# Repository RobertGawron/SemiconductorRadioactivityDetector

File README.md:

# Semiconductor Radioactivity Detector

## Summary

There are many ways to measure radioactivity levels. Semiconductor detectors sense interactions between ionizing radiation and a p-n junction. Since most hobbyists use Geiger-Muller-based detectors (which are lamp-based devices, not semiconductors), I think it's a cool idea to explore this semiconductor-based approach.

## System Architecture

## Additional sub-components used

### Hardware Data Logger

A pulse counter based on the STM32 and ESP chips that can send the measurements via WiFi for further processing, store them on an SD card, or display them to the user. This is an [open-source and open-hardware project that I created, available on GitHub.](https://github.com/RobertGawron/HardwareDataLogger)

### Auxiliary Board (Power Supply + Logic Level Converter)

An auxiliary board was developed later on to fix things that weren’t included on the original board (because it's easier to add a new board than to rework the whole device). This board isn’t really a successful one, but it does its job. It has:

**12V power supply (powered from a 15V wall adapter).** The device needs a very low-noise power supply. Originally, it was powered by a high-quality lab power supply. However, to make it more versatile, I tried using a cheap Chinese power supply and add a board with a power regulator. 

In the first revision, I chose the NCP1117 stabiliser, but it was too noisy. This caused the sensor's output to oscillate randomly, which made the device rather pointless. I made it work by adding plenty of capacitors on the input and output, though this was always a temporary solution. 

In the new version, I will be replacing it with the TPS7A2601DRVR.

**Logic level converter,** to convert logic levels from 12V (high) and 0V (low)—as output by the sensor—to 3.3V (high) and 0V (low), which is standard for STM32 and cheap Chinese logic analyzers. 

In the first version, I just used an open-collector configuration, but this made the device unable to work directly with cheap 3.3V logic analyzers, which need either 0V (low state) or 3.3V (high state).

In the new version, I added a cheap 3.3V stabiliser to provide the correct high state.

## Hardware

All hardware was done using KiCad.

The sensor assembly needs care, as this device is extremely sensitive; [more details are presented in this README.](./Hardware/SemiconductorRadioactivityDetector/README.md)

The sensor circuit is shown below.

The new design of the auxiliary board is shown below, integrated with the whole device. It's the small PCB on the right side of the image. The render was done using Blender.

Circuit of the Auxiliary Board is shown below.

## Mechanic

Before ordering PCBs and the 3D print for the auxiliary holder, how could I be sure everything would fit? Instead of redoing things many times, I took the model of the old PCB, the new PCB that would be the addition to it, the 3D holder, and the metal enclosure (which is a popular consumer enclosure), placed them all accordingly in Blender, and checked if everything fit.

[The needed tools and the workflow are presented in this README.](./Mechanic/README.md)

## Software

[There are some Python and R scripts available](./Software/DataAcquisition/) for gathering data from the device. These were developed during the initial testing phase and may still be useful due to their simplicity.

In the future, the goal is to transition to using the [Hardware Data Logger](https://github.com/RobertGawron/HardwareDataLogger), which provides a more versatile and efficient way to collect measurements.

## Project History

 * [First Unsuccessful Attempts](https://robertgawron.blogspot.com/2016/12/semiconductor-radioactivity-detector.html)
semiconductor-radioactivity-detector.html) - the biggest issue was the lack of proper shielding. Due to the extremely high amplification levels, the device either failed to function or began oscillating uncontrollably without adequate shielding.
* [First Working Version](https://robertgawron.blogspot.com/2019/02/semiconductor-radioactivity-detector.html) - this was a simplified version of the current project. It lacked both polarization voltage and an ADC converter, but it laid the foundation for further improvements.

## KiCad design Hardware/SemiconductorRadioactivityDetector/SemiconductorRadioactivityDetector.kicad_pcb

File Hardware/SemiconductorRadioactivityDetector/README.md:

# Extra Modifications

* The device needs to be completely shielded from sunlight and electromagnetic interference. It should be placed in a grounded metal case. Where the sensor is located, a hole should be drilled and covered with aluminum foil. This taped hole is necessary because the metal enclosure is too thick and would block too much of the radiation. The foil is needed because the signal from sunlight is much stronger, and it would overwhelm the sensor, effectively turning it into a light detector.
* As close as possible to the input power socket, I placed 1n/16V and 100n/16V capacitors in parallel. Without them, the device began oscillating randomly.
* A Schottky diode is connected in series after the extra capacitors mentioned above to reduce the risk of damaging the device when the power supply is connected incorrectly. I'm not sure if it will help enough, but I’ve already damaged one PCB this way, so now it's included.

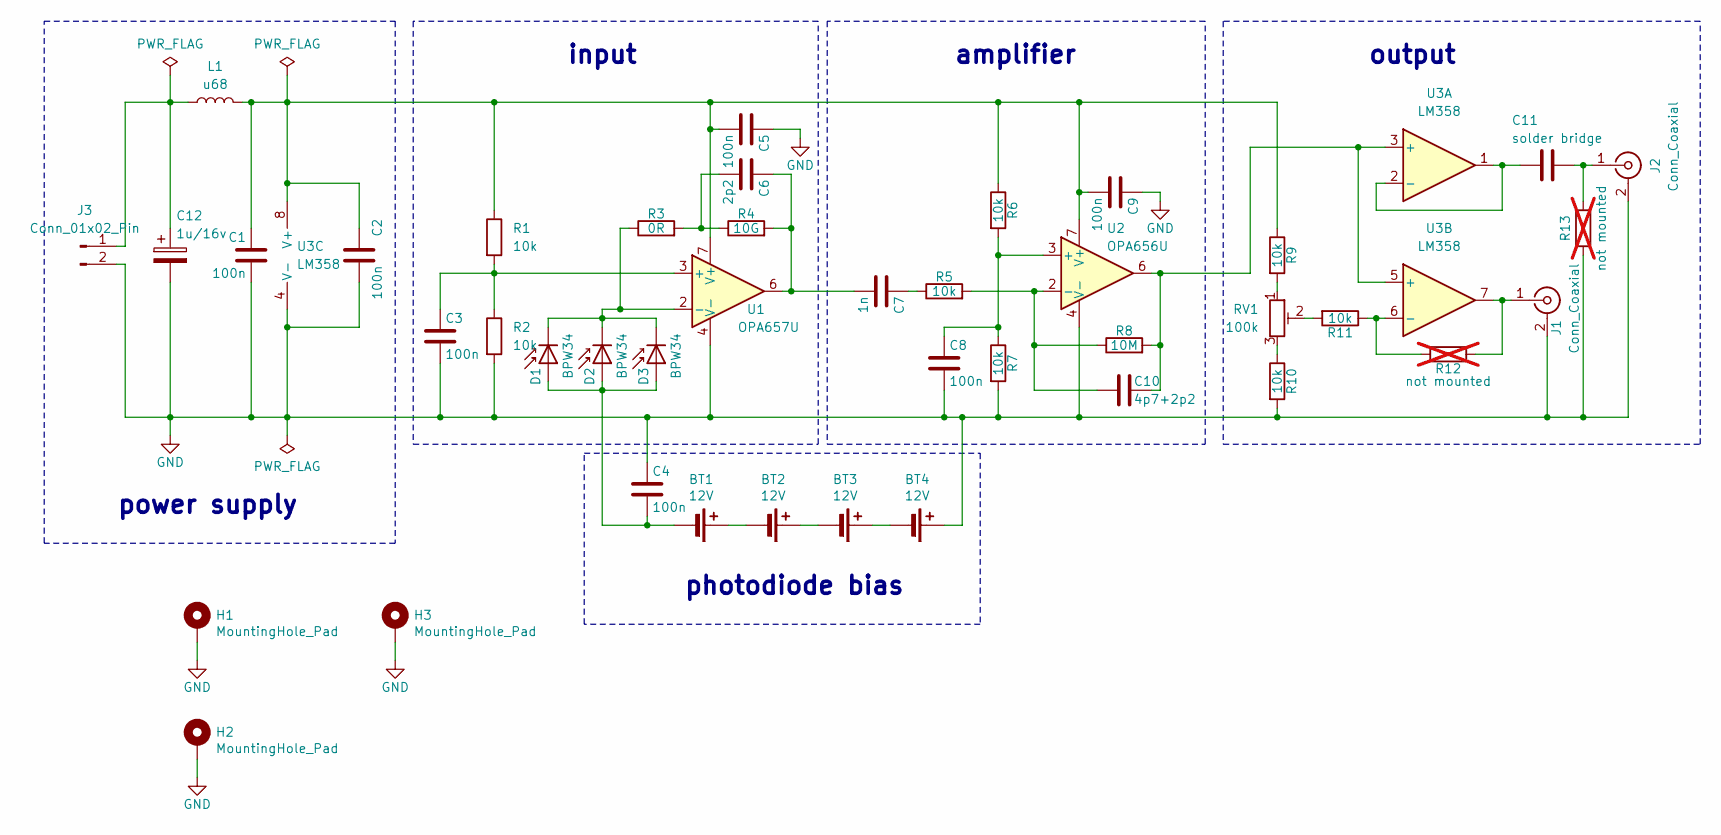
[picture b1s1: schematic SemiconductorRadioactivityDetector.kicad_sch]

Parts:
BT1, BT2, BT3, BT4: 12V; A23Single
C1, C3, C4, C5, C8: 100n; C_0805_2012Metric
C2, C9: 100n; C_0805_HandSoldering
C6: 2p2; C_0805_2012Metric
C7: 1n; C_0805_2012Metric
C10: 4p7+2p2; C_0805_HandSoldering
C11: solder bridge; C_0805_2012Metric
C12: 1u/16v; CP_EIA-3216-18_Kemet-A
D1, D2, D3: BPW34; D_DO-35_SOD27_P5.08mm_Vertical_KathodeUp
H1, H2, H3: MountingHole_Pad; MountingHole_3.5mm_Pad
J1, J2: Conn_Coaxial; BNC_PanelMountable_Vertical
J3: Conn_01x02_Pin; PinHeader_1x02_P2.54mm_Vertical
L1: u68; L_1812_4532Metric
R1, R2, R5, R7, R9, R10, R11: 10k; R_0805_HandSoldering
R3: 0R; R_0805_HandSoldering
R4: 10G; R_0805_HandSoldering
R6: 10k; R_Axial_DIN0207_L6.3mm_D2.5mm_P10.16mm_Horizontal
R8: 10M; R_0805_HandSoldering
R12, R13: not mounted; R_0805_HandSoldering; not fitted
RV1: 100k; Potentiometer_Bourns_3296W_Vertical
U1: OPA657U; SOIC-8_3.9x4.9mm_Pitch1.27mm
U2: OPA656U; SOIC-8_3.9x4.9mm_Pitch1.27mm
U3: LM358; SOIC-8_3.9x4.9mm_P1.27mm

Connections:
GND: BT4.1 (+), C1.2, C2.2, C3.2, C4.1, C5.1, C8.2, C9.1, C12.2, H1.1, H2.1, H3.1, J1.2 (Ext), J2.2 (Ext), J3.2, R2.2, R7.2, R10.2, R13.2, U1.4 (V-), U2.4 (V-), U3.4 (V-)
unnamed: BT1.1 (+), BT2.2 (-)
unnamed: BT1.2 (-), C4.2, D1.2 (A), D2.2 (A), D3.2 (A)
unnamed: BT2.1 (+), BT3.2 (-)
unnamed: BT3.1 (+), BT4.2 (-)
unnamed: C6.1, C7.2, R4.2, U1.6
unnamed: C6.2, R3.2, R4.1
unnamed: C7.1, R5.1
unnamed: D1.1 (K), D2.1 (K), D3.1 (K), R3.1, U1.2 (-)
unnamed: J1.1 (In), R12.1, U3.7
unnamed: C11.1, J2.1 (In), R13.1
unnamed: C12.1, J3.1, L1.1
unnamed: R9.2, RV1.1
unnamed: R10.1, RV1.3
unnamed: R11.2, RV1.2
unnamed: C3.1, R1.2, R2.1, U1.3 (+)
unnamed: C1.1, C2.1, C5.2, C9.2, L1.2, R1.1, R6.1, R9.1, U1.7 (V+), U2.7 (V+), U3.8 (V+)
unnamed: C8.1, R6.2, R7.1, U2.3 (+)
unnamed: C10.2, R5.2, R8.1, U2.2 (-)
unnamed: C10.1, R8.2, U2.6, U3.3 (+), U3.5 (+)
unnamed: C11.2, U3.1, U3.2 (-)
unnamed: R11.1, R12.2, U3.6 (-)

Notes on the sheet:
input
amplifier
power supply
output
photodiode bias

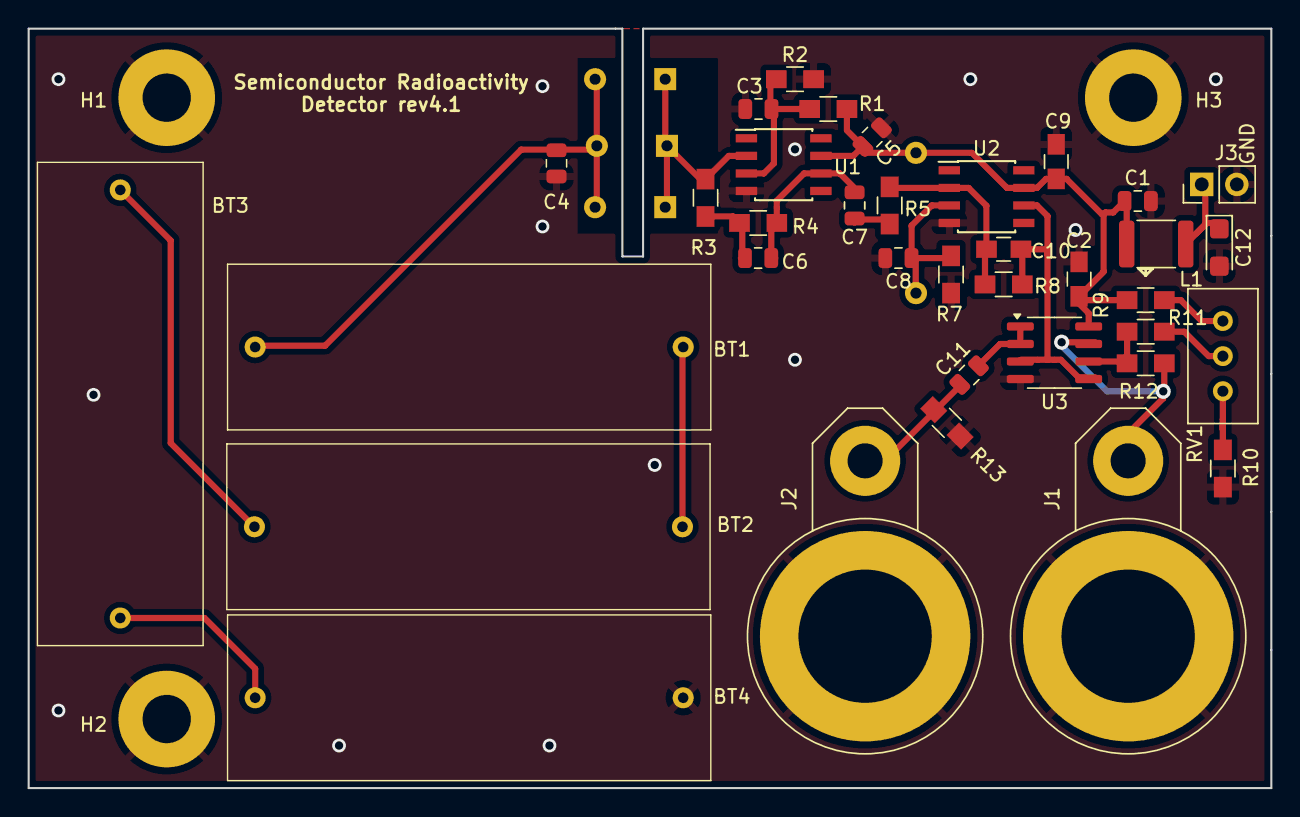
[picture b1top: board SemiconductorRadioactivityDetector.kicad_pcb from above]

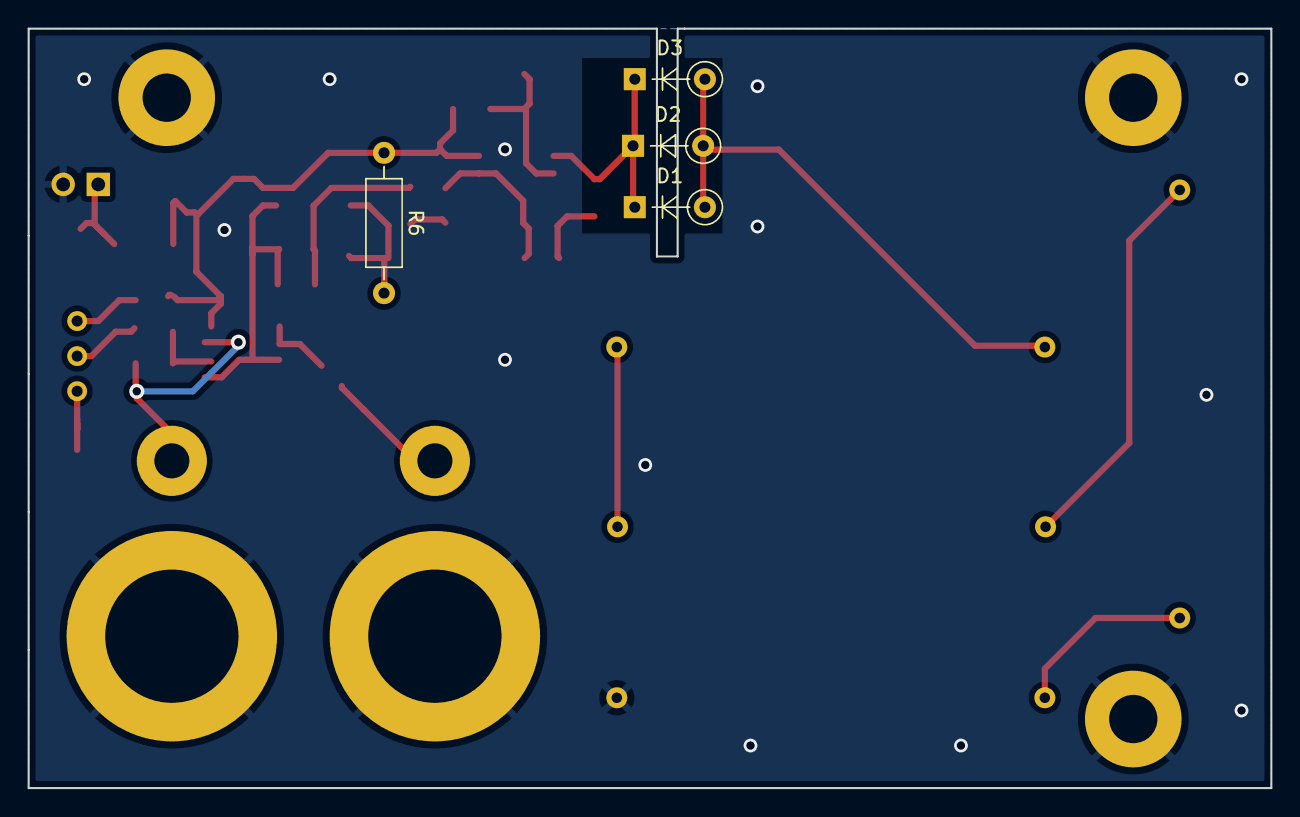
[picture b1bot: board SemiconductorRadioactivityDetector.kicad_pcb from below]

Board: 2 copper layers, 90.0 x 55.0 mm, 43 parts (4 on the bottom side), 22 nets.

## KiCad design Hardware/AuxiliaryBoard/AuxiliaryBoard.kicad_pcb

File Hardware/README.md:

# Hardware

* [Semiconductor Radioactivity Detector](./SemiconductorRadioactivityDetector) - the main project for the sensor.
* [Power Supply + Logic Level Converter](./PowerSupply/) - auxiliary board to provide stable and low-noise power to the sensor, and to convert logic levels from 12V (high) and 0V (low) — as output by the sensor — to 3.3V (high) and 0V (low), which is standard for STM32 and cheap Chinese logic analyzers.

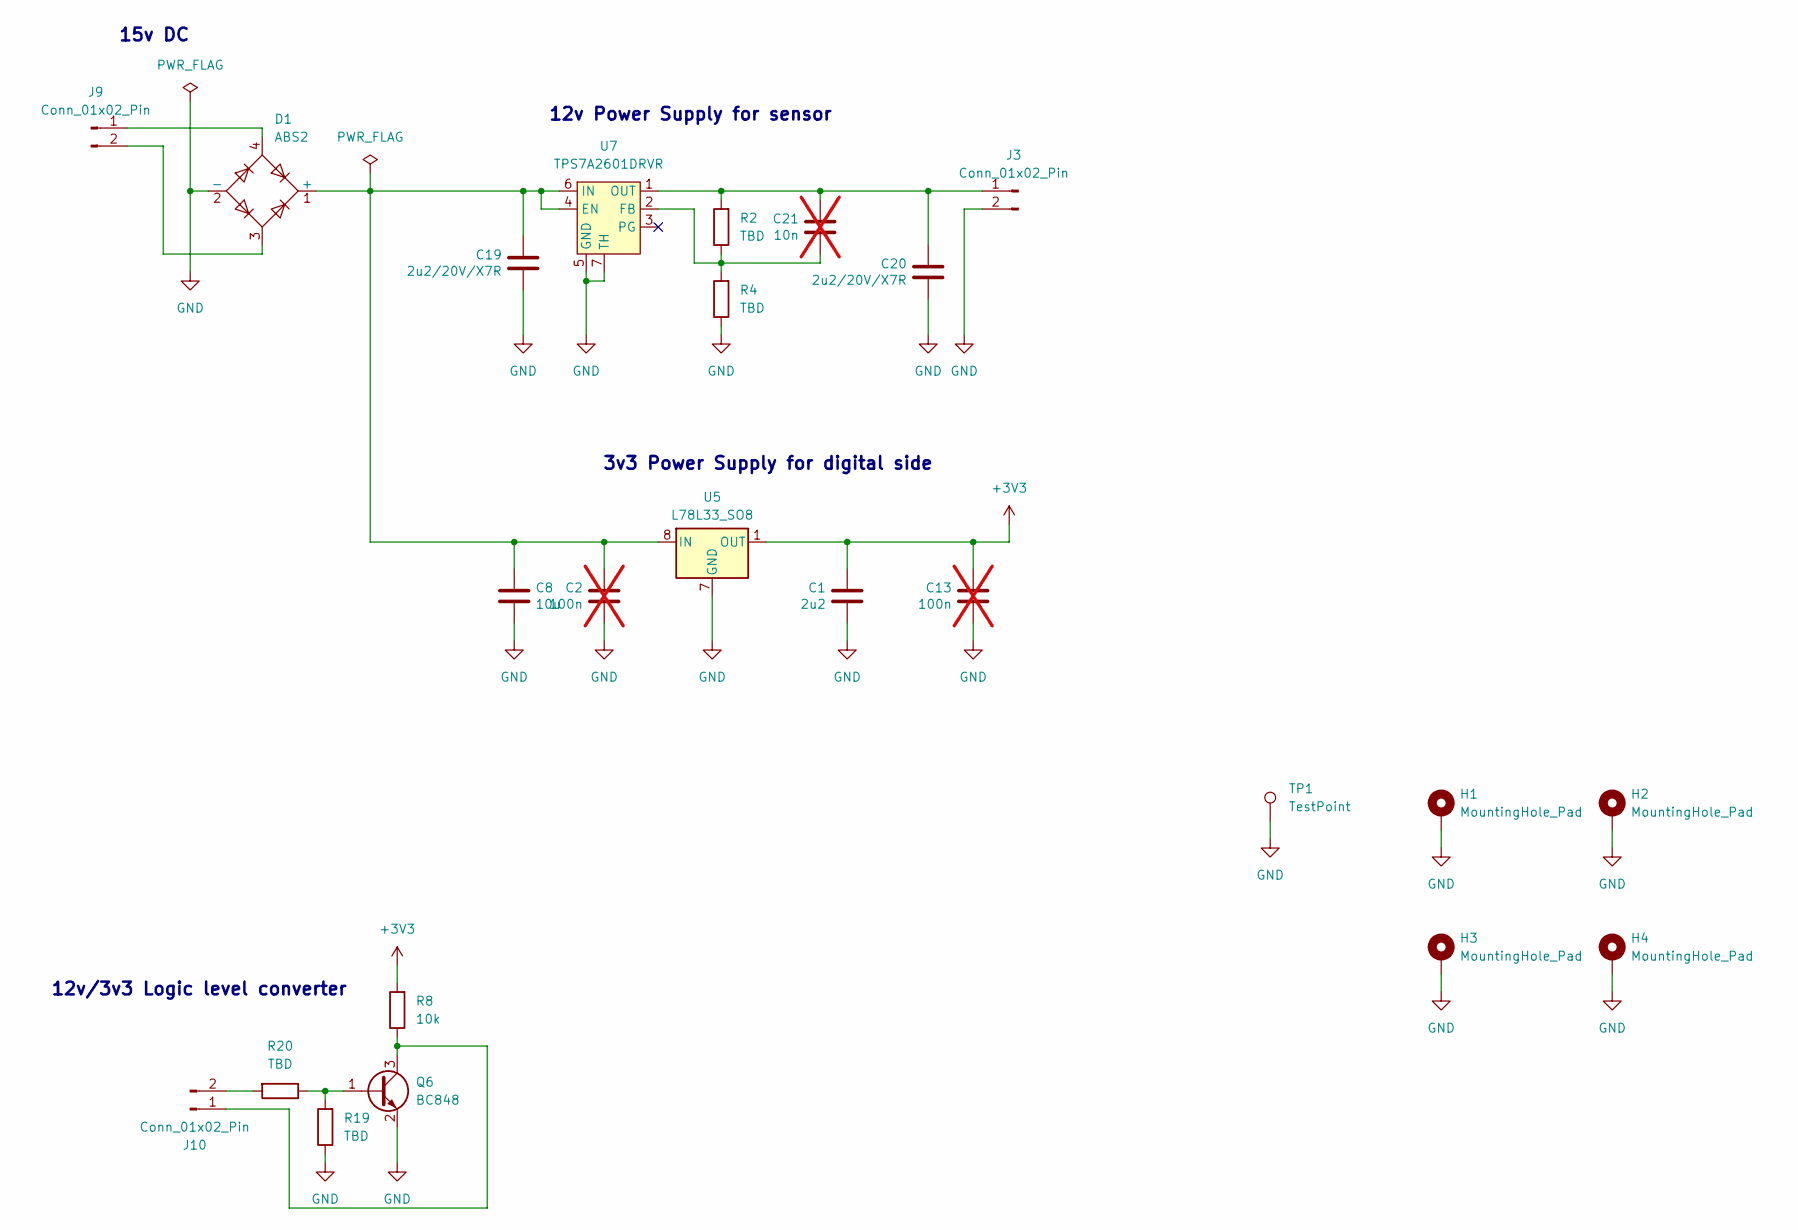
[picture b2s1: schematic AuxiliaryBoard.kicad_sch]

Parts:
C1: 2u2; C_0805_2012Metric
C2, C13: 100n; C_0805_2012Metric; not fitted
C8: 10u; C_0805_2012Metric
C19, C20: 2u2/20V/X7R; C_0805_2012Metric
C21: 10n; C_0805_2012Metric; not fitted
D1: ABS2; Diode_Bridge_Diotec_ABS
H1, H2, H3, H4: MountingHole_Pad; MountingHole_2.5mm_Pad
J3, J9, J10: Conn_01x02_Pin; PinHeader_1x02_P2.54mm_Horizontal
Q6: BC848; SOT-23
R2, R4, R19, R20: TBD; R_0805_2012Metric
R8: 10k; R_0805_2012Metric
TP1: TestPoint; TestPoint_Pad_D2.0mm
U5: L78L33_SO8; SOIC-8_3.9x4.9mm_P1.27mm
U7: TPS7A2601DRVR; WSON-6-1EP_2x2mm_P0.65mm_EP1x1.6mm

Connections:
+3V3: C1.1, C13.1, R8.2, U5.1 (OUT)
GND: C1.2, C2.2, C8.2, C13.2, C19.2, C20.2, D1.2 (-), H1.1, H2.1, H3.1, H4.1, J3.2, Q6.2 (E), R4.1, R19.1, TP1.1, U5.2 (GND), U5.3 (GND), U5.6 (GND), U5.7 (GND), U7.5 (GND), U7.7 (TH)
unnamed: C2.1, C8.1, C19.1, D1.1 (+), U5.8 (IN), U7.4 (EN), U7.6 (IN)
unnamed: C20.1, C21.1, J3.1, R2.2, U7.1 (OUT)
unnamed: D1.4, J9.1
unnamed: D1.3, J9.2
unnamed: J10.1, Q6.3 (C), R8.1
unnamed: J10.2, R20.2
unnamed: Q6.1 (B), R19.2, R20.1
unnamed: C21.2, R2.1, R4.2, U7.2 (FB)

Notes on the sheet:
12v/3v3 Logic level converter
3v3 Power Supply for digital side
12v Power Supply for sensor
15v DC

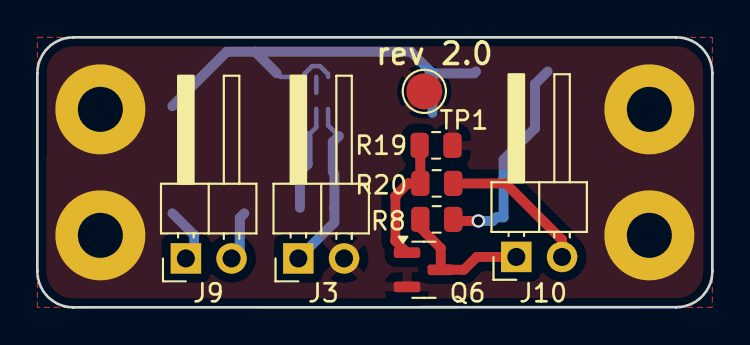
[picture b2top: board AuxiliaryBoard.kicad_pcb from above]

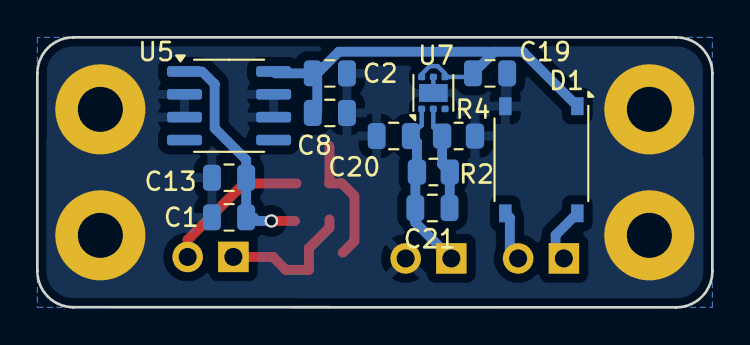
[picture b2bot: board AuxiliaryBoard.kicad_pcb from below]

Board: 2 copper layers, 37.5 x 15.0 mm, 24 parts (12 on the bottom side), 10 nets.

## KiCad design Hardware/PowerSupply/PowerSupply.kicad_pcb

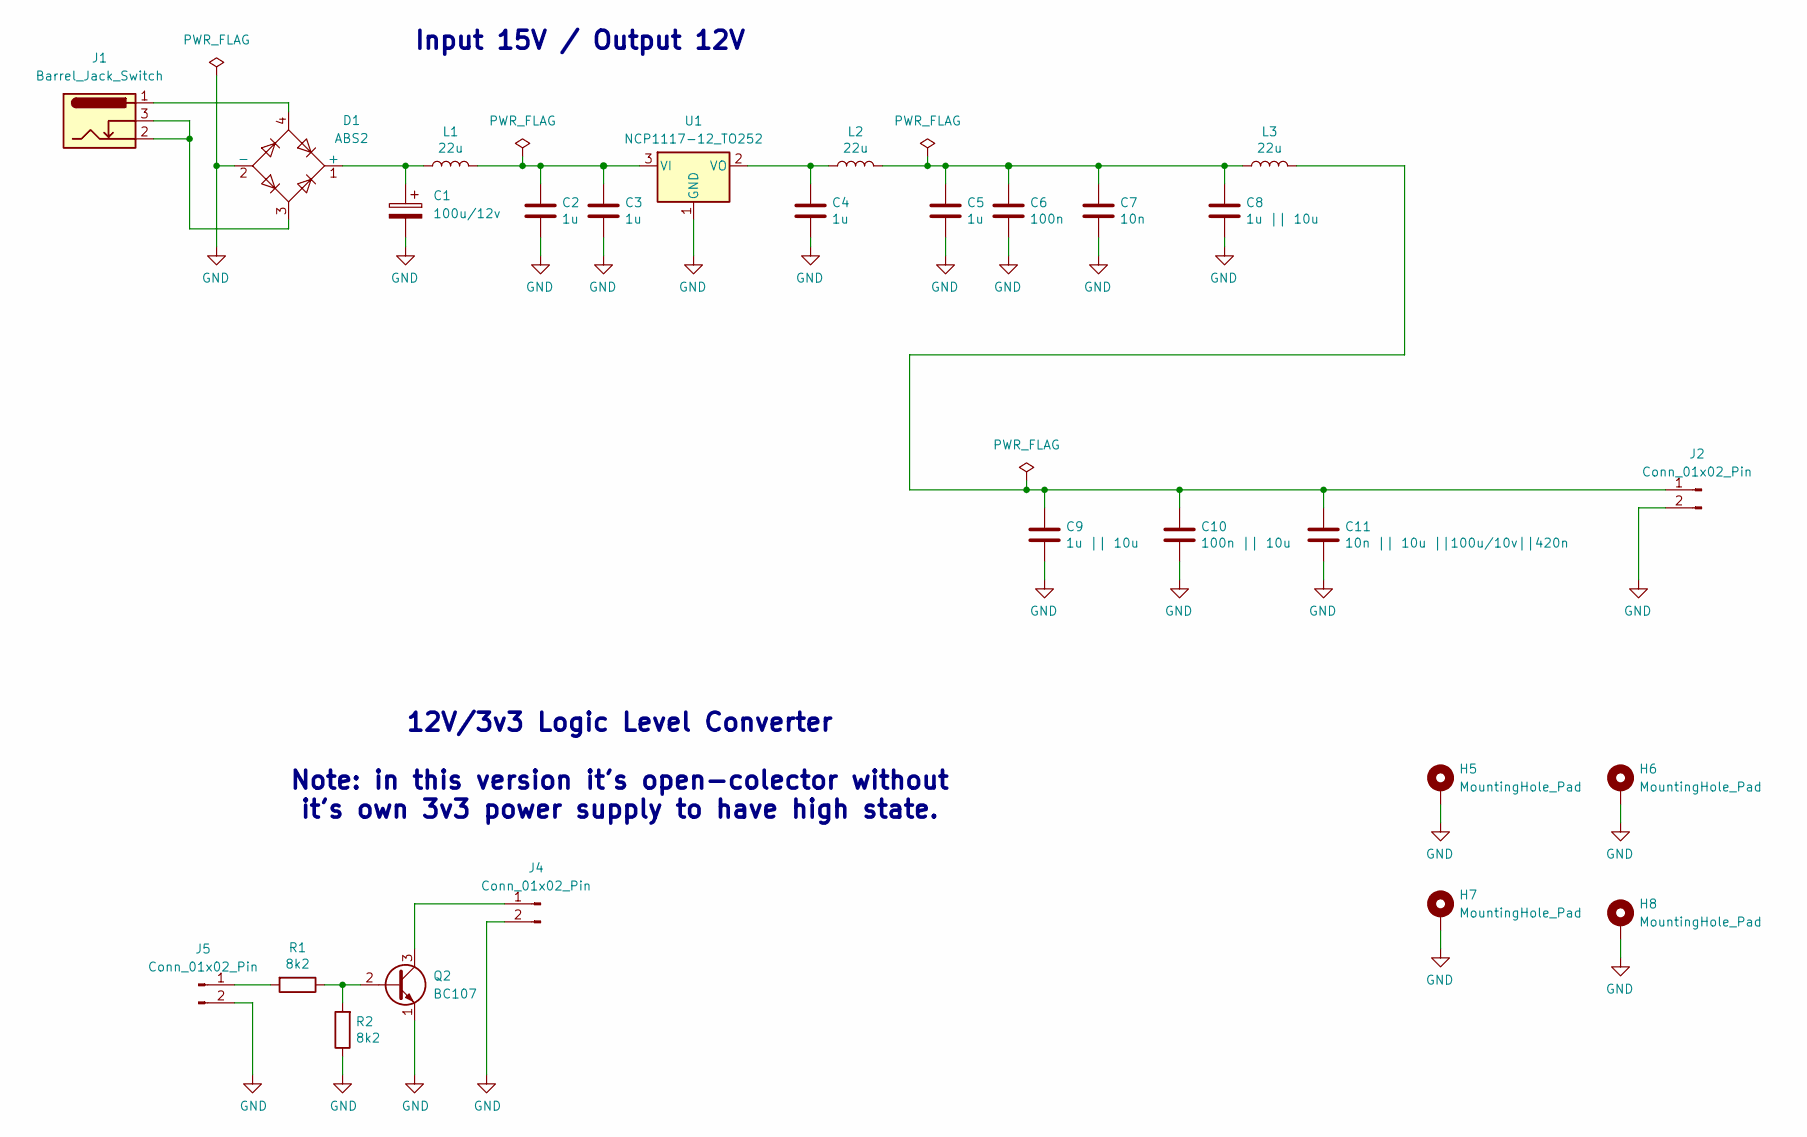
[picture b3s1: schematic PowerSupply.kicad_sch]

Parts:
C1: 100u/12v; C_Radial_D6.3mm_H5.0mm_P2.50mm
C2, C3, C4, C5: 1u; C_0805_2012Metric
C6: 100n; C_0805_2012Metric
C7: 10n; C_0805_2012Metric
C8, C9: 1u || 10u; C_0805_2012Metric
C10: 100n || 10u; C_0805_2012Metric
C11: 10n || 10u ||100u/10v||420n; C_0805_2012Metric
D1: ABS2; Diode_Bridge_Diotec_ABS
H5, H6, H7, H8: MountingHole_Pad; MountingHole_3.5mm_Pad
J1: Barrel_Jack_Switch; BarrelJack_GCT_DCJ200-10-A_Horizontal
J2, J4, J5: Conn_01x02_Pin; PinHeader_1x02_P2.54mm_Vertical
L1, L2, L3: 22u; L_7.3x7.3_H3.5
Q2: BC107; TO-18-3
R1, R2: 8k2; R_0805_2012Metric
U1: NCP1117-12_TO252; SOT-23-3

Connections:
GND: C1.2, C2.2, C3.2, C4.2, C5.2, C6.2, C7.2, C8.2, C9.2, C10.2, C11.2, D1.2 (-), H5.1, H6.1, H7.1, H8.1, J2.2, J4.2, J5.2, Q2.1 (E), R2.1, U1.1 (GND)
unnamed: C5.1, C6.1, C7.1, C8.1, L2.1, L3.2
unnamed: C1.1, D1.1 (+), L1.2
unnamed: D1.3, J1.2, J1.3
unnamed: D1.4, J1.1
unnamed: C9.1, C10.1, C11.1, J2.1, L3.1
unnamed: J4.1, Q2.3 (C)
unnamed: J5.1, R1.2
unnamed: Q2.2 (B), R1.1, R2.2
unnamed: C2.1, C3.1, L1.1, U1.3 (VI)
unnamed: C4.1, L2.2, U1.2 (VO)

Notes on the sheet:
12V/3v3 Logic Level Converter Note: in this version it's open-colector without it's own 3v3 power supply to have high state.
Input 15V / Output 12V

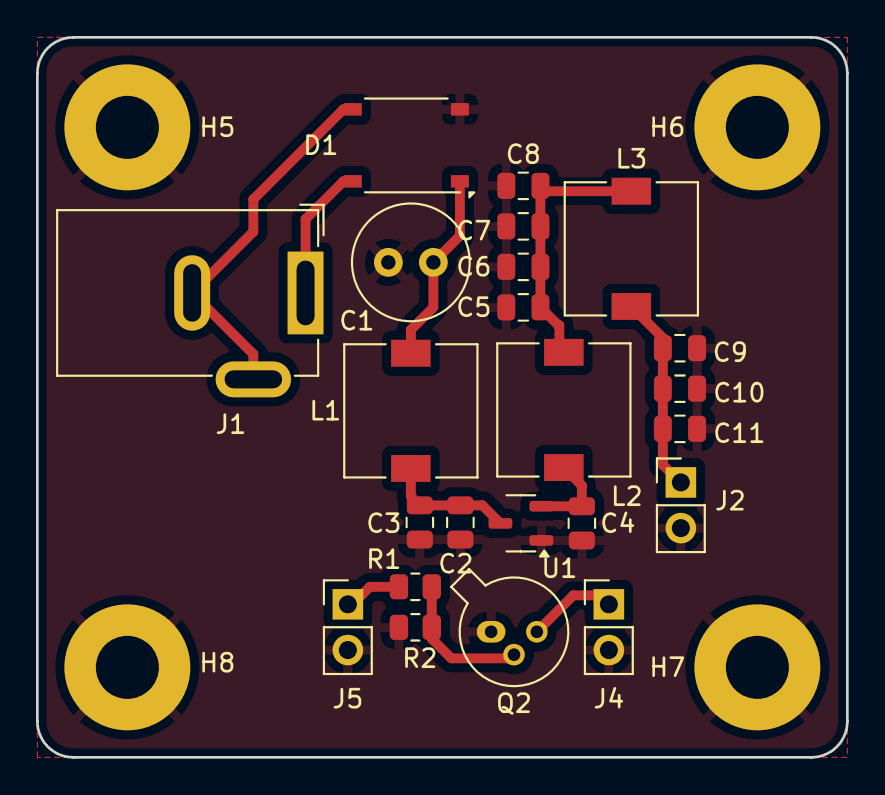
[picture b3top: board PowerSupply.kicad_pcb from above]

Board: 2 copper layers, 45.0 x 40.0 mm, 27 parts (0 on the bottom side), 11 nets.

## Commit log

2017-01-14 Initial commit.
2018-05-27 Removed old obsolete version.
2018-05-27 New HW version.
2018-09-15 cleanup in docs
2018-09-18 pcb fixes before sending to factory
2018-09-19 final touch before ordering pcb
2018-09-19 Create LICENSE
2019-02-16 initial versionwq
2019-02-16 added files to parse results
2019-02-16 scripts to create diagrams
2019-02-17 automated .png generation
2019-02-17 added architecture of raspbbery pi app
2019-02-24 fixed missing libraries
2019-02-24 last touch before sending to pcb factory
2019-02-24 added clearance
2019-05-03 fixes after hw assembly and tests
2019-06-04 removed junk files, added gitignore
2019-08-11 add sections to readme
2019-08-11 fix #18
2019-08-11 fix #23
2019-08-11 forder structure cleanup
2019-08-11 better folder name
2019-08-11 unified names with other my repos
2019-08-11 reworked architecture diagram
2019-08-11 fix #19 #20
2019-08-11 infor about sw architecture
2019-08-11 build latex documents
2019-08-11 added CI
2019-08-11 fix to work with travis
2019-08-11 fix typos
2019-08-11 more redable
2019-08-11 fix #34
2019-09-08 fix #37
2019-09-08 sensor moved to its own subdirectory
2019-09-08 added logic converter project
2020-06-01 add basic simulator of digital filters
2020-10-15 Squashed 'Software/HardwareDataLogger/' content from commit 37d90c3
    git-subtree-dir: Software/HardwareDataLogger
    git-subtree-split: 37d90c36ef6dff2428dff3a75682a6a990aea3fe
2020-10-15 exclude external repo from language statistics
2020-10-17 remove old subrepo version
2020-10-17 Squashed 'Software/HardwareDataLogger/' content from commit 36e64a0
    git-subtree-dir: Software/HardwareDataLogger
    git-subtree-split: 36e64a0b74689bc3145da8180f2f13aac98a8adf
2020-10-22 move from travis to guthub actions
2020-10-22 add README.md
2020-10-22 docs update
2020-10-23 link build status to project's build section
2020-10-24 move (for diagrams) from .png to .svg
2020-10-24 move (for diagrams) from .png to .svg - add missing update
2020-10-24 Squashed 'Software/HardwareDataLogger/' changes from 36e64a0..dc3c36e
2020-10-24 Squashed 'Software/HardwareDataLogger/' changes from 36e64a0..dc3c36e
    dc3c36e Merge pull request #21 from RobertGawron/develop
    a8342c6 Merge pull request #20 from RobertGawron/feature/add_contionous_integration
    304d8cd fix c linter issues
    4a7e1a6 Merge pull request #19 from RobertGawron/develop
    1880f22 Merge pull request #18 from RobertGawron/feature/add_contionous_integration
    7c2c33d exclude external libs from repo programming language statistics
2020-11-06 Fix grammar mistakes (found by Code Spell Checker add-on in VSCode). (fix #62)
2020-11-06 Squashed 'Software/HardwareDataLogger/' changes from dc3c36e..58e2b47
    58e2b47 Merge pull request #24 from RobertGawron/develop
    74d7174 Merge pull request #23 from RobertGawron/fix/remove_gammar_mistakes
    8752828 Fix grammar mistakes (found by Code Spell Checker add-on in VSCode). (fix #22)
    git-subtree-dir: Software/HardwareDataLogger
    git-subtree-split: 58e2b477f2824c01ec6d98d952829f0472e2d4a0
2024-09-15 transition to kicad8 and docs cleanup
2025-06-08 auxiliary board rev1.0
2025-09-14 auxiliary board rev2 + its 3d printed holder
2026-02-07 remove obsolete files
